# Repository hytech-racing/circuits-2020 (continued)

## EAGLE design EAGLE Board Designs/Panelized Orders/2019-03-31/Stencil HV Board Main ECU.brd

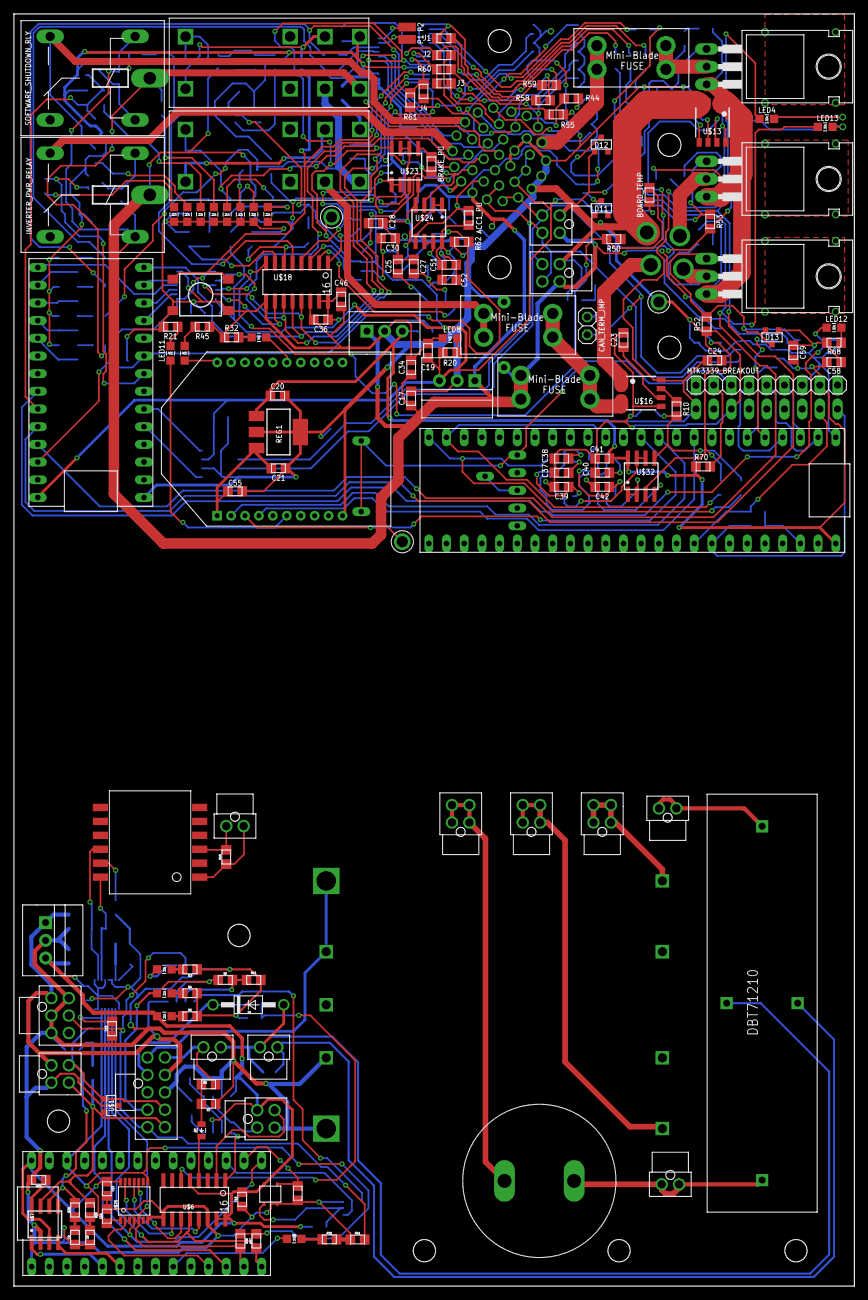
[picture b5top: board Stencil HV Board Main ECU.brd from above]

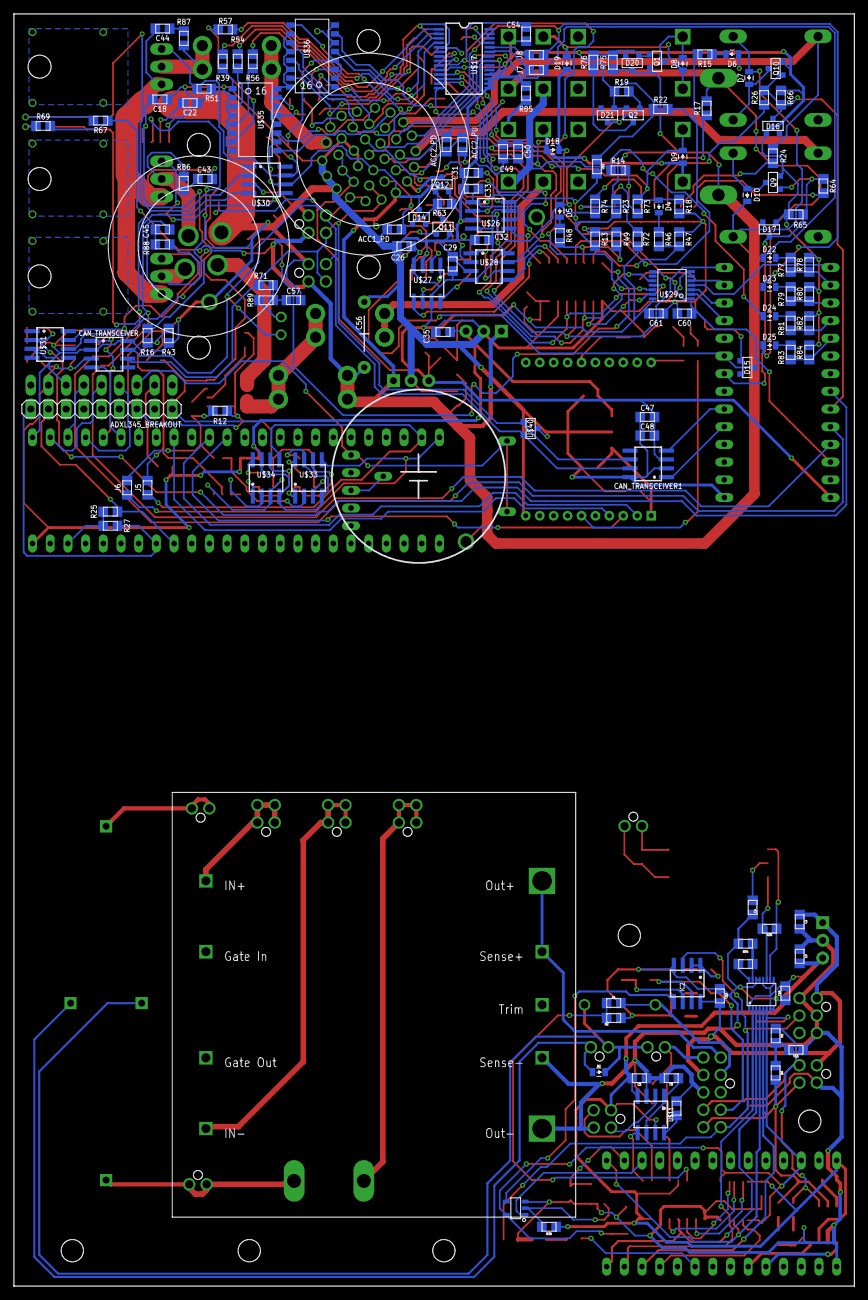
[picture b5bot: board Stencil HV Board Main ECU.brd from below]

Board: 2 copper layers, 120.7 x 182.6 mm, 291 parts (143 on the bottom side), 228 nets.

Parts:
5ABOARDFUSE, 5AFUSE, 5ASHUTDOWNFUSE: MINI-BLADE_FUSE_HOLDER
ACC1_PD, ACC1_PU, ACC2_PD, ACC2_PU: 10k; 0805
ADXL345_BREAKOUT: 1X09
BMS-OK: GREEN; LED-805
BMS_SHUTDOWN_RLY: RT424012; RELAY_DPDT
BOARD_TEMP: THERMISTOR_NCP210805; 0805
BRAKE_PU: 10k; 0805
C1: 180µF; LLS2V221MELZ
C2, C3, C17, C19, C34, C35: 10uF; 0805
C4: 27pF; 0805
C5, C6, C10, C12, C13, C14, C15, C16, C18, C24, C46, C54, C55: 0.1uF; 0805
C7: 530pF; 0805
C8, C9: 560pF; 0805
C11, C57: 4.7nF; 0805
C20, C21, C36, C47, C49, C51, C53, C58: 1uF; 0805
C22, C23, C25, C28, C31: 47nF; 0805
C26, C27, C29, C30, C32, C33, C38, C39, C41, C42, C48, C50, C52, C59, C60, C61: .1uF; 0805
C37, C40: 470pF; 0805
C43, C44, C45: 0805
C56: 470uF; CAP-PTH-LARGE
CAN_TERM_JMP: M02_SLIM; 1X02_SLIM
CAN_TRANSCEIVER, CAN_TRANSCEIVER1: MCP2551; SOIC-08
CURRENT: CURRENT; NANO-FIT_VERTICAL-4
D1: DIODE; DO-41
D2, D3, D4, D5, D6, D7, D8, D9, D10, D18, D19, D22, D23, D24, D25: TS4148 RYG; 0805_D
D11, D12, D13, D14, D15, D16, D17, D20, D21: MMBZ5246BLT1G; SOT23
DISCH+: DISCHARGE+; NANO-FIT_VERTICAL-2
HV+FUSED_1A-IMD+: HV+; NANO-FIT_VERTICAL-4
HV+UNFUSED: HV+UNFUSED; NANO-FIT_VERTICAL-2
HV-FUSED_1A-IMD-: HV-; NANO-FIT_VERTICAL-4
HV-UNFUSED_DISCHARGE-: HV-UNFUSED; NANO-FIT_VERTICAL-4
IC1: OKI-78SR-5; OKI-78SR
IC2: NE5532SOIC; SOIC-08
IMD: CONNECTOR-6NANO-FIT_VERTICAL-6; NANO-FIT_VERTICAL-6
IMD-OK: YELLOW; LED-805
IMD_SHUTDOWN_RLY: RT424009; RELAY_DPDT
INTERLOCK: INTERLOCK; NANO-FIT_VERTICAL-2
INVERTER_PWR_RELAY: G5LE; ZF112
ISO_SPI: ISO_SPI; NANO-FIT_VERTICAL-2
J1, J2, J3, J4, J5, J6, J7, J8: JUMPER; 0805
LED: BLUE; LED-805
LED1: White; LED-805
LED3, LED7, LED11: Green; LED-805
LED4, LED6, LED10, LED12, LED13, LED17, LED18: Red; LED-805
LED5, LED9: Yellow; LED-805
LED8: Purple; LED-805
LED14: Blue; LED-805
MAIN: MAIN; NANO-FIT_VERTICAL-10
MTK3339_BREAKOUT: 1X09
ON-LED: PURPLE; LED-805
P1, P2: SOLDER_PAD; SOLDER_PAD_XSMALL
POWER: POWER; NANO-FIT_VERTICAL-4
Q1, Q12: P-CHANNEL_MOSFET_DMP3099L-7; SOT23
Q2, Q9, Q10, Q11: SOT23
R1, R6, R15, R23, R46, R48, R77, R79, R81, R83: 43k; 0805
R2, R7, R13, R22, R47, R49, R78, R80, R82, R84: 12k; 0805
R3: 820; 0805
R4: 5k; 0805
R5, R20: 270; 0805
R8, R9, R71, R89: 60; 0805
R10, R16: 1K; 0805
R11, R30, R33, R34, R76: 1k; 0805
R12, R43: 2K; 0805
R14, R18, R36, R37, R41, R73: 2k; 0805
R17: 20k; 0805
R19, R42, R50, R51, R52, R53, R62, R63, R65, R66, R70, R75: 10k; 0805
R21, R74: 33; 0805
R24: 6.8k; 0805
R25, R27: 4.7k; 0805
R26: 1.2K; 0805
R28, R29, R40: 100; 0805
R31: 43; 0805
R32, R64, R67, R68, R69: 1.2k; 0805
R35: 120; 0805
R38: 430; 0805
R39, R54, R56, R57, R58, R59, R60, R61: 150; 0805
R44, R45, R55: 0; 0805
R72: 5.1k; 0805
R85: 20; 0805
R86, R87, R88: 0805
REG, REG3: 5V; OKI-78SR
REG1: LM3940; SOT223
RELAYS: RELAYS; NANO-FIT_VERTICAL-2
RF: 2k; 0805
S1: TACTILE_SWITCH_SMD_6.2MM_TALL
SOFTWARE_SHUTDOWN_RLY: G5LE; ZF112
U$1, U$40: CDSOT23-T24CAN-Q; SOT23
U$2: HM2102NLT
U$3: SN74LVC1G08; SOT-23-5
U$4: DBT71210
U$5: HV_DCDC_VI-J71-CZ
U$6, U$18: MCP3208SOIC; SOIC-16
U$7: MCP2551; SOIC-08
U$8: LTC6820; MSOP-16
U$9, U$12: TEENSY_3.2_SIMPLE
U$10: STWD100; SOT23-5
U$11: MAX7480; SOIC-08
U$13, U$16: ACS715_CURRENT_SENSOR; SOP8
U$14: TEENSY_3.5_EXT
U$15: XBEE
U$17: MCP23S17SSOP28; SSOP28
U$19, U$20, U$21: N-CHANNEL_MOSFET_IRF1324PBF; TO-220-H-HOLE
U$22: CR-2450/G1AN
U$23, U$24, U$32: MCP6002SOIC; SOIC-08
U$25, U$29: TXB0104TSSOP; TSSOP-14
U$26, U$27, U$28, U$33, U$34: SOIC-08
U$30, U$31: MC34152; SOIC-08
U$35, U$36: TLP291-4; 11-11F1
U$37, U$38, U$39: TEST_POINT
X1: CONNECTOR-37; AUTOSPORT_14-35
X2: CONNECTOR-4AUTOSPORT; AUTOSPORT_12-04
X3, X4: CONNECTOR-4NANO-FIT-VERTICAL-4; NANO-FIT_VERTICAL-4

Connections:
3.3V: R25.2, R27.2, U$14.3.3V
3.3V_MAIN_TEENSY: C60.1, U$12.3.3V, U$29.1, U$29.8
12VIN: U$16.1, U$16.2, X2.P$1
12VSUPPLY_DIV: C53.2, R13.1, R23.2, U$23.3
12VSUPPLY_READ: U$18.4, U$23.1, U$23.2
12VUNFUSED: 5ABOARDFUSE.L1, 5ABOARDFUSE.L2, 5ASHUTDOWNFUSE.L1, 5ASHUTDOWNFUSE.L2, U$16.3, U$16.4
+3V3: C14.1, C15.2, R36.1, R37.1, U$3.5, U$8.6, U$9.3.3V, U$25.1, U$25.8
+5V: C3.1, C5.1, C10.1, C13.1, C16.2, CURRENT.P$1, IC1.3, ON-LED.A, R38.1, U$6.5, U$6.15, U$6.16, U$7.3, U$8.1, U$8.7, U$8.8, U$8.9, U$8.12, U$9.VIN, U$10.VCC, U$11.4, U$11.7, U$25.14
+5V1: ACC1_PU.2, ACC2_PU.2, BOARD_TEMP.1, BRAKE_PU.2, C19.2, C26.1, C29.1, C32.1, C36.2, C46.2, C47.2, C48.2, C49.2, C50.2, C51.1, C52.1, C54.1, C61.1, CAN_TRANSCEIVER1.3, R20.1, R72.1, REG.3, U$12.VIN, U$17.9, U$17.18, U$18.15, U$18.16, U$23.8, U$24.8, U$26.4, U$26.7, U$27.4, U$27.7, U$28.4, U$28.7, U$29.14, U$38.P$1, X1.P$27, X1.P$28, X1.P$29
+12V: C2.1, C12.1, IC1.1, IC2.8, IMD.P$1, MAIN.P$7, POWER.P$1
+12V1: 5ABOARDFUSE.R1, 5ABOARDFUSE.R2, C17.2, C34.2, C56.1, D7.C, D10.C, D14.3, D20.3, INVERTER_PWR_RELAY.1, INVERTER_PWR_RELAY.P, Q1.2, Q12.2, R23.1, R63.1, R75.1, REG.1, REG3.1, SOFTWARE_SHUTDOWN_RLY.2, U$30.6, U$31.6, U$35.10, U$35.12, U$35.14, U$35.16, U$36.10, U$36.12, U$36.14, U$36.16, U$37.P$1, X1.P$10, X1.P$34, X3.P$1, X4.P$1
BMS_OK: D5.A, D21.3, Q2.1, R19.1, R74.1, X1.P$31
BMS_OK_3.3V: IC2.5, U$3.4
BMS_OK_10V: BMS-OK.A, IC2.7, MAIN.P$4, RF.2
BMS_OK_READ: R48.2, R49.1, U$18.6
BMS_OK_SW: BMS_SHUTDOWN_RLY.COIL+, D8.C, Q1.3
BMS_PWR_STEP: BMS_SHUTDOWN_RLY.3, BMS_SHUTDOWN_RLY.COIL-, D8.A, D19.A
BRAKE_LIGHT: Q12.3, X1.P$9
BRAKE_LIGHT_CTRL: D15.3, Q11.1, R62.2, U$12.D7(RX3)
CANH: MAIN.P$10, POWER.P$4, R8.2, R28.2, U$1.2, U$7.7
CANH1: CAN_TERM_JMP.1, CAN_TRANSCEIVER.7, CAN_TRANSCEIVER1.7, U$40.2, X1.P$12, X1.P$13, X3.P$4, X4.P$4
CANL: MAIN.P$9, POWER.P$3, R9.2, R29.2, U$1.1, U$7.6
CANL1: CAN_TRANSCEIVER.6, CAN_TRANSCEIVER1.6, R71.1, U$40.1, X1.P$11, X1.P$26, X3.P$3, X4.P$3
CHARGE_ENABLE: D1.C, MAIN.P$2, R1.1
COOLINGSENSE: J5.2, R16.2, R43.2, U$32.3
COOLINGSENSE_FILT: J5.1, U$14.A12, U$34.5
CS1_5V: U$18.10, U$29.13
CS1_TEENSY: U$12.D9(RX2), U$29.2
CS2_5V: U$17.11, U$29.12
CS2_TEENSY: U$12.D10(TX2), U$29.3
CS_LTC6820: U$8.5, U$9.D10(TX2)
CS_MCP3208_3.3V: U$9.D9(RX2), U$25.2
CURRENTSENSE2: C43.2, C44.2, C45.2, U$13.1, U$13.2, U$19.3, U$20.3, U$21.3
CUR_SENSE: CURRENT.P$2, U$11.2
DASH11_READ: R77.2, R78.1, U$12.A0
DASH12_READ: R79.2, R80.1, U$12.A1
DASH_1_EXTERN: R44.2, X1.P$1
DASH_1_INTER: R39.1, U$17.1
DASH_2_EXTERN: R55.2, X1.P$2
DASH_2_INTER: R54.1, U$17.2
DASH_3_EXTERN: U$35.11, X1.P$3
DASH_3_INTER: R56.1, U$17.3
DASH_4_EXTERN: U$35.9, X1.P$4
DASH_4_INTER: R57.1, U$17.4
DASH_5_EXTERN: J1.1, U$36.15, X1.P$18
DASH_5_INTER: J1.2, R58.1, U$17.5
DASH_6_EXTERN: J2.1, U$36.13, X1.P$19
DASH_6_INTER: J2.2, R59.1, U$17.6
DASH_7_EXTERN: J3.1, U$36.11, X1.P$20
DASH_7_INTER: J3.2, R60.1, U$17.7
DASH_8_EXTERN: J4.1, U$36.9, X1.P$21
DASH_8_INTER: J4.2, R61.1, U$17.8
DASH_9_EXTERN: U$17.21, X1.P$23
DASH_10_EXTERN: U$17.22, X1.P$32
DASH_11_EXTERN: D22.A, J7.1, X1.P$6
DASH_11_INTER: J7.2, U$17.23
DASH_12_EXTERN: D23.A, J8.1, X1.P$22
DASH_12_INTER: J8.2, U$17.24
DISCHARGE_RELAY_GND: D2.A, RELAYS.P$2, U$4.COIL-
ECUSENSE: J6.2, R10.2, R12.2, U$32.5
ECUSENSE_FILT: J6.1, U$14.A13, U$33.5
FAN1-: 5AFUSE.R1, 5AFUSE.R2, R87.1, U$20.2
FAN1CONTROL: LED4.A, U$12.A8, U$30.2
FAN1DRIVE: D12.3, R51.2, U$20.1, U$30.7
FAN2-: R86.1, U$19.2, X2.P$3
FAN2CONTROL: LED13.A, U$12.A9, U$30.4
FAN2DRIVE: D11.3, R53.2, U$19.1, U$30.5
GND: C2.2, C3.2, C4.2, C5.2, C6.2, C7.2, C8.1, C9.1, C10.2, C11.1, C12.2, C13.2, C14.2, C15.1, C16.1, CURRENT.P$4, IC1.2, IC2.4, IMD.P$2, IMD.P$3, IMD.P$4, MAIN.P$8, POWER.P$2, R2.1, R3.1, R4.2, R5.2, R7.1, R11.1, R30.1, R31.2, R34.2, R41.2, R42.2, U$1.3, U$3.3, U$5.8SENSE-, U$5.9VOUT-, U$6.9, U$6.14, U$7.2, U$8.13, U$8.14, U$9.GND, U$10.EN, U$10.GND, U$11.3, U$25.7
GND1: ACC1_PD.2, ACC2_PD.2, ADXL345_BREAKOUT.3, BMS_SHUTDOWN_RLY.4, C17.1, C18.2, C19.1, C20.2, C21.1, C22.2, C23.2, C24.2, C25.2, C26.2, C27.1, C28.2, C29.2, C30.1, C31.2, C32.2, C33.1, C34.1, C35.1, C36.1, C37.2, C38.2, C39.1, C40.2, C41.2, C42.1, C46.1, C47.1, C48.1, C49.1, C50.1, C51.2, C52.2, C53.1, C54.2, C55.2, C56.2, C57.2, C58.1, C59.1, C60.2, C61.2, CAN_TRANSCEIVER.2, CAN_TRANSCEIVER.8, CAN_TRANSCEIVER1.2, CAN_TRANSCEIVER1.8, D11.1, D12.1, D13.1, D15.1, D16.1, D17.1, D21.1, LED3.C, LED5.C, LED6.C, LED7.C, LED8.C, LED9.C, LED17.C, LED18.C, MTK3339_BREAKOUT.7, Q2.2, Q9.2, Q10.2, Q11.2, R12.1, R13.2, R18.2, R19.2, R21.1, R22.2, R32.1, R43.1, R45.1, R47.2, R49.2, R50.1, R51.1, R52.1, R53.1, R62.1, R65.2, R66.2, R67.2, R68.2, R69.2, R78.2, R80.2, R82.2, R84.2, R85.2, REG.2, REG1.2, REG1.4, REG3.2, S1.B1, S1.B2, U$12.GND, U$13.3, U$13.4, U$13.5, U$14.GND, U$15.10, U$16.5, U$17.10, U$17.15, U$17.16, U$17.17, U$18.9, U$18.14, U$23.4, U$24.4, U$26.3, U$27.3, U$28.3, U$29.7, U$30.3, U$31.3, U$32.4, U$33.3, U$34.3, U$35.2, U$35.4, U$35.6, U$35.8, U$36.2, U$36.4, U$36.6, U$36.8, U$39.P$1, U$40.3, X1.P$14, X1.P$15, X1.P$16, X1.P$30, X1.P$35, X1.P$36, X2.P$4, X3.P$2, X4.P$2
HV+FUSED_1A: HV+FUSED_1A-IMD+.P$1, HV+FUSED_1A-IMD+.P$2, HV+FUSED_1A-IMD+.P$3, HV+FUSED_1A-IMD+.P$4, U$5.1VIN+
HV+UNFUSED: C1.P$1, HV+UNFUSED.P$1, HV+UNFUSED.P$2, U$4.CONTACT1
HV+UNFUSED_FSAE_DISCHARGE: DISCH+.P$1, DISCH+.P$2, U$4.CONTACT2
HV-FUSED_1A: HV-FUSED_1A-IMD-.P$1, HV-FUSED_1A-IMD-.P$2, HV-FUSED_1A-IMD-.P$3, HV-FUSED_1A-IMD-.P$4, U$5.4VIN-
HV-UNFUSED: C1.P$2, HV-UNFUSED_DISCHARGE-.P$1, HV-UNFUSED_DISCHARGE-.P$2, HV-UNFUSED_DISCHARGE-.P$3, HV-UNFUSED_DISCHARGE-.P$4
IM: R35.1, U$2.P$10, U$8.10
IMD_PWR_STEP: D9.A, D18.A, IMD_SHUTDOWN_RLY.3, IMD_SHUTDOWN_RLY.COIL-
INVERTER_CTRL: D17.3, Q9.1, R64.1, R65.1, U$12.D6
INVERTER_SUPPLY: INVERTER_PWR_RELAY.S, X1.P$7
IP: R35.2, U$2.P$12, U$8.11
ISOSPI-M: ISO_SPI.P$2, R40.2, U$2.P$3
ISOSPI-P: ISO_SPI.P$1, R40.1, U$2.P$1
LATCH_EXT_BUTTON: D18.C, D19.C, LED1.C, S1.A1, S1.A2, X1.P$37
MISO: R37.2, U$6.12, U$8.3, U$9.D12
MISO_TEENSY: U$12.D12, U$17.14, U$18.12
MOSI_5V: U$6.11, U$25.10
MOSI_5V1: U$17.13, U$18.11, U$29.10
MOSI_TEENSY: R36.2, U$8.2, U$9.D11, U$25.5
MOSI_TEENSY1: U$12.D11, U$29.5
MTK3339_DIN: MTK3339_BREAKOUT.6, U$14.D1(TX1)
MTK3339_DOUT: MTK3339_BREAKOUT.5, U$14.D0(RX1)
MTK3339_FIX: MTK3339_BREAKOUT.4, U$14.D2
unnamed: U$6.1, U$11.5
unnamed: C6.1, U$11.1, U$11.6
unnamed: ON-LED.C, R5.1
unnamed: C7.1, U$11.8
unnamed: LED7.A, R17.2
unnamed: LED18.A, R24.2
unnamed: U$6.10, U$25.13
unnamed: LED8.A, R20.2
unnamed: D3.A, R6.2, R7.2
unnamed: D3.C, U$6.4
unnamed: C11.2, R8.1, R9.1
unnamed: IC2.6, R11.2, RF.1
unnamed: R10.1, U$16.7
unnamed: R16.1, U$13.7
unnamed: C23.1, U$16.6
unnamed: CAN_TRANSCEIVER.4, U$14.D4(CANRX)
unnamed: CAN_TRANSCEIVER.1, U$14.D3(CANTX)
unnamed: CAN_TRANSCEIVER1.4, U$12.D4(CANRX)
unnamed: LED5.A, R14.2
unnamed: U$24.6, U$24.7, U$27.2
unnamed: U$23.6, U$23.7, U$26.2
unnamed: CAN_TRANSCEIVER1.1, U$12.D3(CANTX)
unnamed: U$24.1, U$24.2, U$28.2
unnamed: R1.2, R2.2, U$6.6
unnamed: U$7.1, U$9.D3(CANTX)
unnamed: R30.2, U$7.8
unnamed: C8.2, R28.1
unnamed: C9.2, R29.1
unnamed: LED.C, R31.1
unnamed: D4.C, R46.1
unnamed: R33.1, U$8.16
unnamed: R33.2, R34.1, U$8.15
unnamed: D5.C, R48.1
unnamed: D6.C, R15.1
unnamed: C4.1, U$2.P$11
unnamed: U$7.4, U$9.D4(CANRX)
unnamed: LED.A, U$9.D7(RX3)
unnamed: R38.2, U$3.2, U$10.WDO
unnamed: LED11.C, R21.2
unnamed: U$3.1, U$9.A1
unnamed: LED10.C, R32.2
unnamed: IC2.1, IC2.2, IMD-OK.A
unnamed: LED14.C, R45.2
unnamed: BMS-OK.C, R4.1
unnamed: IMD-OK.C, R3.2
unnamed: LED17.A, R26.2
unnamed: LED11.A, U$15.6
unnamed: C22.1, U$13.6
unnamed: LED10.A, U$15.15
unnamed: R42.1, U$9.A0, U$10.WDI
unnamed: R39.2, U$35.1
unnamed: 5AFUSE.L1, 5AFUSE.L2, X1.P$17
unnamed: C27.2, U$27.1, U$27.6
unnamed: C25.1, U$27.8
unnamed: C30.2, U$28.1, U$28.6
unnamed: C28.1, U$28.8
unnamed: C33.2, U$26.1, U$26.6
unnamed: C31.1, U$26.8
unnamed: R44.1, U$35.15
unnamed: R54.2, U$35.3
unnamed: R55.1, U$35.13
unnamed: R56.2, U$35.5
unnamed: LED14.A, U$15.20
unnamed: R57.2, U$35.7
unnamed: R58.2, U$36.1
unnamed: R59.2, U$36.3
unnamed: R60.2, U$36.5
unnamed: R61.2, U$36.7
unnamed: D14.1, Q11.3, Q12.1, R63.2
unnamed: LED6.A, R64.2
unnamed: U$14.GND_2, U$22.-
unnamed: D10.A, INVERTER_PWR_RELAY.2, Q9.3
unnamed: D7.A, Q10.3, SOFTWARE_SHUTDOWN_RLY.1
unnamed: U$32.1, U$32.2, U$34.2
unnamed: U$32.6, U$32.7, U$33.2
unnamed: C39.2, U$33.1, U$33.6
unnamed: C37.1, U$33.8
unnamed: C42.2, U$34.1, U$34.6
unnamed: C40.1, U$34.8
unnamed: LED4.C, R67.1
unnamed: LED12.C, R68.1
unnamed: LED13.C, R69.1
unnamed: MTK3339_BREAKOUT.2, R70.2
unnamed: LED1.A, R72.2
unnamed: LED9.A, R73.2
unnamed: LED3.A, R74.2
unnamed: D20.1, Q1.1, R75.2, R76.2
unnamed: Q2.3, R76.1
unnamed: D22.C, R77.1
unnamed: D23.C, R79.1
unnamed: D24.C, R81.1
unnamed: D25.C, R83.1
unnamed: IMD_SHUTDOWN_RLY.4, R85.1
unnamed: P1.P$1, U$17.25
unnamed: P2.P$1, U$17.26
unnamed: C44.1, R87.2
unnamed: C43.1, R86.2
unnamed: C45.1, R88.2
unnamed: CAN_TERM_JMP.2, R89.2
unnamed: C57.1, R71.2, R89.1
OKHS: IC2.3, IMD.P$5, MAIN.P$5, R41.1
OKHS1: D4.A, D9.C, IMD_SHUTDOWN_RLY.COIL+, R18.1, R73.1, X1.P$33
OKHS_READ: R46.2, R47.1, U$18.7
PUMP1-: R88.1, U$21.2, X2.P$2
PUMPCONTROL: LED12.A, U$12.A6, U$31.2
PUMPDRIVE: D13.3, R52.2, U$21.1, U$31.7
READ_ACCEL1: U$18.2, U$27.5
READ_ACCEL2: U$18.3, U$28.5
READ_BRAKE: U$18.1, U$26.5
SCK_5V: U$6.13, U$25.11
SCK_5V1: U$17.12, U$18.13, U$29.11
SCK_TEENSY: U$8.4, U$9.D13, U$25.4
SCK_TEENSY1: U$12.D13, U$29.4
SCL: ADXL345_BREAKOUT.9, R27.1, U$14.A5
SDA: ADXL345_BREAKOUT.8, R25.1, U$14.A4
SHUTDOWN_A: 5ASHUTDOWNFUSE.R1, 5ASHUTDOWNFUSE.R2, IMD_SHUTDOWN_RLY.6
SHUTDOWN_B: BMS_SHUTDOWN_RLY.6, D24.A, IMD_SHUTDOWN_RLY.5, R14.1
SHUTDOWN_B_READ: R81.2, R82.1, U$12.A2
SHUTDOWN_C: BMS_SHUTDOWN_RLY.5, D25.A, R17.1, SOFTWARE_SHUTDOWN_RLY.P
SHUTDOWN_C_READ: R83.2, R84.1, U$12.A3
SHUTDOWN_D: D6.A, R24.1, SOFTWARE_SHUTDOWN_RLY.S, X1.P$5
SHUTDOWN_G: INTERLOCK.P$1, MAIN.P$6, R6.1
SHUTDOWN_H: D1.A, D2.C, INTERLOCK.P$2, RELAYS.P$1, U$4.COIL+
SHUTDOWN_OUT_READ: R15.2, R22.1, U$18.5
SIGNAL_ACCEL1: ACC1_PD.1, ACC1_PU.1, U$24.5, X1.P$25
SIGNAL_ACCEL2: ACC2_PD.1, ACC2_PU.1, U$24.3, X1.P$24
SIGNAL_BRAKE: BRAKE_PU.1, U$23.5, X1.P$8
SOFTWARE_SHUTDOWN: D16.3, Q10.1, R26.1, R66.1, U$12.A7
TELEMETRY5V: ADXL345_BREAKOUT.1, C18.1, C20.1, C24.1, C35.2, C38.1, C41.1, C58.2, C59.2, CAN_TRANSCEIVER.3, MTK3339_BREAKOUT.8, R70.1, REG1.1, REG3.3, U$13.8, U$14.VIN, U$16.8, U$32.8, U$33.4, U$33.7, U$34.4, U$34.7
TEMPSENSE: BOARD_TEMP.2, R50.2, U$18.8
TEMP_SENSE: CURRENT.P$3, U$6.2
TSAL+: MAIN.P$1, U$5.5VOUT+, U$5.6SENSE+
VBAT_RTC: MTK3339_BREAKOUT.3, U$14.VBAT, U$22.+_0, U$22.+_1
VCC: C21.2, C55.1, REG1.3, U$15.1
XB8: U$14.D7(RX3), U$15.4
XBDI: U$14.D10(TX2), U$15.3
XBDO: U$14.D9(RX2), U$15.2

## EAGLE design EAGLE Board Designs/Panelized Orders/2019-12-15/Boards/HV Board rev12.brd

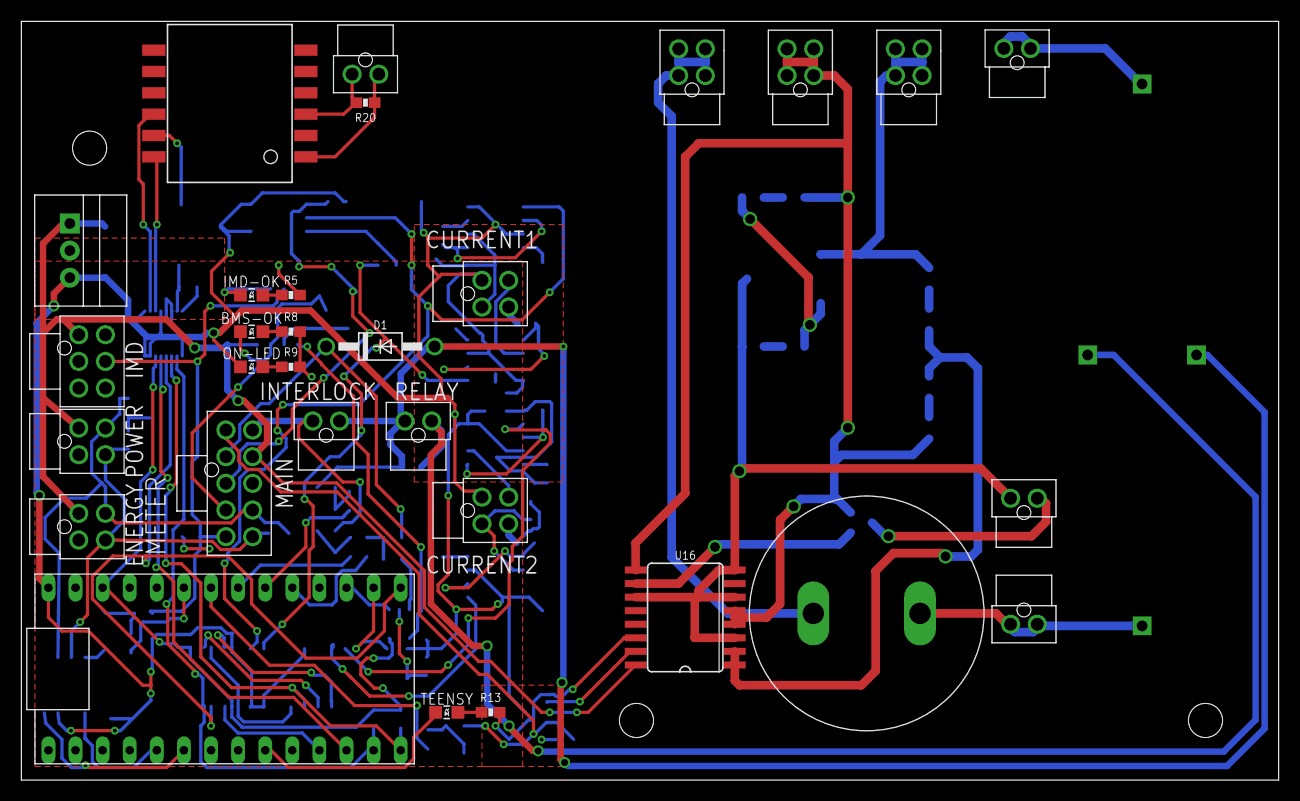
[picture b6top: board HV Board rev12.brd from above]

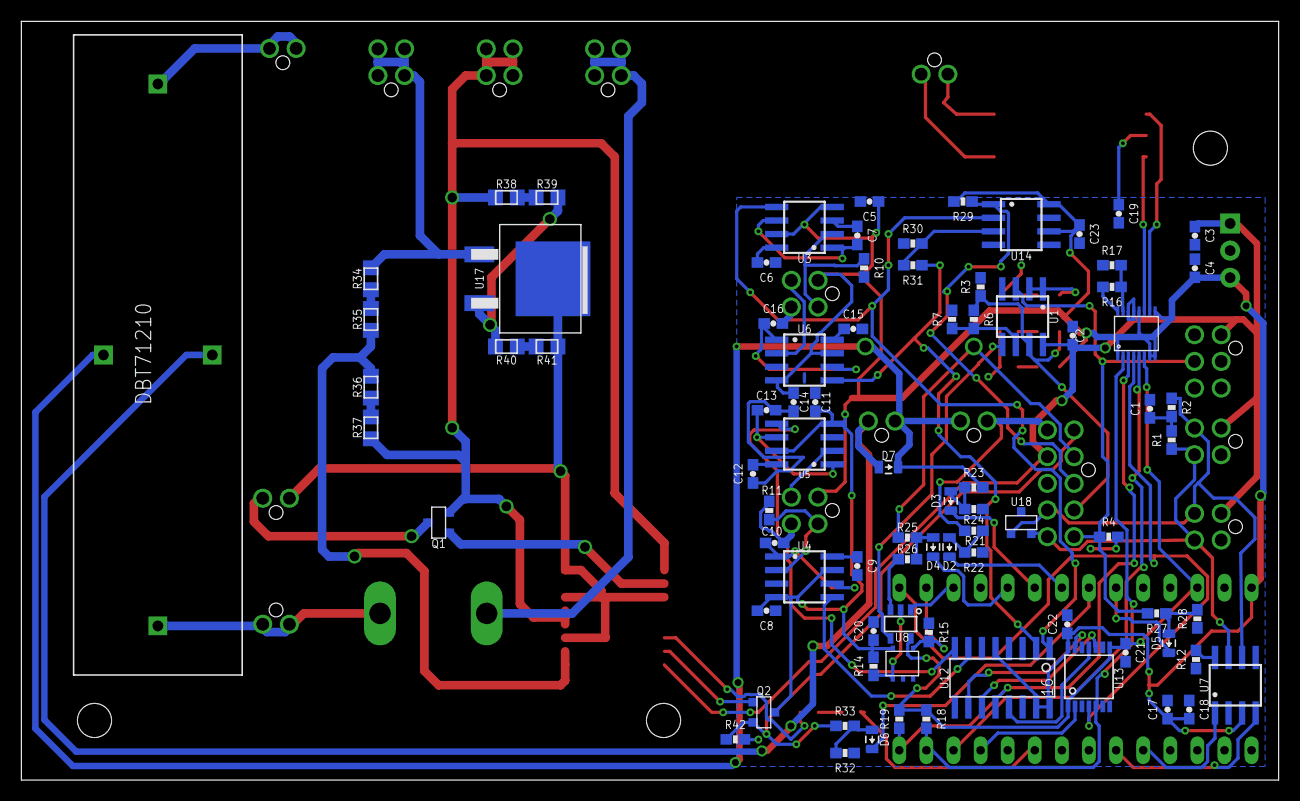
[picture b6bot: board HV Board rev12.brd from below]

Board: 2 copper layers, 117.9 x 71.1 mm, 113 parts (83 on the bottom side), 86 nets.

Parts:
BMS-OK: GREEN; LED-805
C1: 4.7nF; 0603-CAP
C2, C5, C7, C8, C10, C11, C13, C14, C16, C17, C18, C20, C21, C22, C23: 0.1uF; 0603-CAP
C3, C4: 10uF; 0603-CAP
C6, C9, C12, C15: 530pF; 0603-CAP
C19: 27pF; 0603-CAP
C24: 180µF; LLS2V221MELZ
CURRENT1, CURRENT2: CURRENT; NANO-FIT_VERTICAL-4
D1: DIODE; DO-41
D2, D3, D4, D5, D6, D7: TS4148 RYG; 0805_D
DISCH+: DISCHARGE+; NANO-FIT_VERTICAL-2
ENERGYMETER: ENERGY METER; NANO-FIT_VERTICAL-4
HV+FUSED_1A-IMD+: HV+; NANO-FIT_VERTICAL-4
HV+UNFUSED: HV+UNFUSED; NANO-FIT_VERTICAL-2
HV-FUSED_1A-IMD-: HV-; NANO-FIT_VERTICAL-4
HV-UNFUSED_DISCHARGE-: HV-UNFUSED; NANO-FIT_VERTICAL-4
IMD: IMD; NANO-FIT_VERTICAL-6
IMD-OK: YELLOW; LED-805
INDICATOR: INDICATOR; NANO-FIT_VERTICAL-2
INTERLOCK: INTERLOCK; NANO-FIT_VERTICAL-2
ISO_SPI: ISO_SPI; NANO-FIT_VERTICAL-2
MAIN: MAIN; NANO-FIT_VERTICAL-10
ON-LED: PURPLE; LED-805
POWER: POWER; NANO-FIT_VERTICAL-4
Q1, Q2: DMG3406L; SOT23
R1, R2: 60; 0603-RES
R3, R4, R7, R8, R18, R19, R29, R42: 2k; 0603-RES
R5: 820; 0603-RES
R6: 4k; 0603-RES
R9: 270; 0603-RES
R10, R11, R15: 10K; 0603-RES
R12, R16, R17: 1k; 0603-RES
R13: 43; 0603-RES
R14: 430; 0603-RES
R20: 100; 0603-RES
R21, R23, R25, R27: 43k; 0603-RES
R22, R24, R26, R28: 12k; 0603-RES
R30, R32, R33: 5K; 0603-RES
R31: 261; 0603-RES
R34, R35: 510k; 0805
R36: 14k; 0805
R37: 1.4k; 0805
R38, R39: 20k; 0805
R40, R41: 2k; 0805
RELAY: RELAY; NANO-FIT_VERTICAL-2
TEENSY: BLUE; LED-805
TEENSY3.2: TEENSY_3.2_SIMPLE
U1: OPA2172; SOIC-08
U2: OKI-78SR-5; OKI-78SR
U3, U4, U5, U6: MAX7480; SOIC-08
U7: MCP2551; SOIC-08
U8: SN74LVC1G08; SOT-23-5
U9: LTC6820; MSOP-16
U10: STWD100; SOT23-5
U11: HM2102NLT
U12: MCP3208SOIC; SOIC-16
U13: TXB0104TSSOP; TSSOP-14
U14: MCP6542SOIC; SOIC-08
U15: DBT71210
U16: UCC21520A; SO16-DW
U17: LR8; TO-252
U18: CDSOT23-T24CAN-Q; SOT23

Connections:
60V_THRESHOLD_SIGNAL: MAIN.P$1, Q2.2, R33.1, R42.1
60V_THRESHOLD_TEENSY: D6.C, TEENSY3.2.A6
+3V3: C21.1, R18.1, R19.1, TEENSY3.2.3.3V, U8.5, U9.6, U13.1, U13.8
+5V: C4.1, C5.1, C8.1, C11.1, C14.1, C17.1, C18.1, C20.1, C22.1, C23.1, CURRENT1.P$1, CURRENT2.P$1, ON-LED.A, Q2.3, R14.1, R29.2, TEENSY3.2.VIN, U2.3, U3.4, U3.7, U4.4, U4.7, U5.4, U5.7, U6.4, U6.7, U7.3, U9.1, U9.7, U9.8, U9.9, U9.12, U10.VCC, U12.5, U12.15, U12.16, U13.14, U14.6, U14.8
+12V: C2.1, C3.1, ENERGYMETER.P$1, IMD.P$1, MAIN.P$7, POWER.P$1, U1.8, U2.1, U16.16
BMS_OK_3.3V: U1.5, U8.4
BMS_OK_10V: BMS-OK.A, MAIN.P$4, R3.1, R6.2, U1.7
BSPD_CURR_REFERENCE: R30.2, R31.1, U14.3
BSPD_CURR_SIGNAL: MAIN.P$3, R29.1, U14.1
CANH: ENERGYMETER.P$4, MAIN.P$10, POWER.P$4, R1.2, U7.7, U18.2
CANL: ENERGYMETER.P$3, MAIN.P$9, POWER.P$3, R2.2, U7.6, U18.1
CHARGE_ENABLE: D1.C, MAIN.P$2, R25.1
CHARGE_ENABLE_TEENSY: D4.C, TEENSY3.2.A3
CS_LTC6820: TEENSY3.2.D10(TX2), U9.5
CS_MCP3208_3.3V: TEENSY3.2.D9(RX2), U13.2
CURR1_SENSE: CURRENT1.P$2, R10.1, U3.2
CURR1_SENSE_FILTERED: U3.5, U12.1, U14.2
CURR2_SENSE: CURRENT2.P$2, R11.1, U4.2
CURR2_SENSE_FILTERED: U4.5, U12.7
DISCHARGE_RELAY_GND: D7.A, RELAY.P$2, U15.COIL-
GND: C1.1, C2.2, C3.2, C4.2, C5.2, C6.2, C7.2, C8.2, C9.2, C10.2, C11.2, C12.2, C13.2, C14.2, C15.2, C16.2, C17.2, C18.2, C19.2, C20.2, C21.2, C22.2, C23.2, CURRENT1.P$4, CURRENT2.P$4, ENERGYMETER.P$2, IMD.P$2, IMD.P$3, IMD.P$4, MAIN.P$8, POWER.P$2, R3.2, R4.2, R5.1, R7.1, R8.2, R9.2, R10.2, R11.2, R12.1, R13.2, R15.2, R17.2, R22.1, R24.1, R26.1, R28.1, R30.1, R32.1, R42.2, TEENSY3.2.AGND, TEENSY3.2.GND, U1.4, U2.2, U3.3, U4.3, U5.3, U6.3, U7.2, U8.3, U9.13, U9.14, U10.EN, U10.GND, U12.4, U12.9, U12.14, U13.7, U14.4, U14.5, U16.14, U18.3
HV+FUSED_1A: HV+FUSED_1A-IMD+.P$1, HV+FUSED_1A-IMD+.P$2, HV+FUSED_1A-IMD+.P$3, HV+FUSED_1A-IMD+.P$4, R34.2, U17.1
HV+UNFUSED: C24.P$1, HV+UNFUSED.P$1, HV+UNFUSED.P$2, U15.CONTACT1
HV+UNFUSED_FSAE_DISCHARGE: DISCH+.P$1, DISCH+.P$2, U15.CONTACT2
HV-FUSED_1A: HV-FUSED_1A-IMD-.P$1, HV-FUSED_1A-IMD-.P$2, HV-FUSED_1A-IMD-.P$3, HV-FUSED_1A-IMD-.P$4, Q1.2, R37.1, R38.2, U16.4, U16.5, U16.9
HV-UNFUSED: C24.P$2, HV-UNFUSED_DISCHARGE-.P$1, HV-UNFUSED_DISCHARGE-.P$2, HV-UNFUSED_DISCHARGE-.P$3, HV-UNFUSED_DISCHARGE-.P$4
IM: U9.10, U11.P$10
IP: U9.11, U11.P$12
ISOSPI-M: ISO_SPI.P$2, R20.2, U11.P$3
ISOSPI-P: ISO_SPI.P$1, R20.1, U11.P$1
MISO: R19.2, TEENSY3.2.D12, U9.3, U12.12
MOSI_5V: U12.11, U13.10
MOSI_TEENSY: R18.2, TEENSY3.2.D11, U9.2, U13.5
unnamed: INDICATOR.P$2, Q1.3
unnamed: C7.1, U3.1, U3.6
unnamed: ON-LED.C, R9.1
unnamed: C6.1, U3.8
unnamed: U12.10, U13.13
unnamed: D2.A, R21.2, R22.2
unnamed: D4.A, R25.2, R26.2
unnamed: D6.A, R32.2, R33.2
unnamed: C1.2, R1.1, R2.1
unnamed: R6.1, R7.2, U1.6
unnamed: D3.A, R23.2, R24.2
unnamed: R34.1, R35.1
unnamed: R39.1, R40.1, U17.3
unnamed: R35.2, R36.2, U16.1, U16.2
unnamed: R36.1, R37.2
unnamed: Q2.1, U16.15
unnamed: D5.A, R27.2, R28.2
unnamed: Q1.1, U16.10
unnamed: INDICATOR.P$1, R41.2, U16.3, U16.6, U16.8, U16.11, U17.2(TAB)
unnamed: TEENSY3.2.D3(CANTX), U7.1
unnamed: R12.2, U7.8
unnamed: R13.1, TEENSY.C
unnamed: R16.1, U9.16
unnamed: R16.2, R17.1, U9.15
unnamed: C19.1, U11.P$11
unnamed: TEENSY3.2.D4(CANRX), U7.4
unnamed: TEENSY.A, TEENSY3.2.D7(RX3)
unnamed: R14.2, U8.2, U10.WDO
unnamed: TEENSY3.2.A1, U8.1
unnamed: IMD-OK.A, U1.1, U1.2
unnamed: R40.2, R41.1
unnamed: BMS-OK.C, R8.1
unnamed: IMD-OK.C, R5.2
unnamed: R38.1, R39.2
unnamed: C16.1, U6.1, U6.6
unnamed: C15.1, U6.8
unnamed: R15.1, TEENSY3.2.A0, U10.WDI
unnamed: C10.1, U4.1, U4.6
unnamed: C9.1, U4.8
unnamed: C13.1, U5.1, U5.6
unnamed: C12.1, U5.8
OKHS: IMD.P$5, MAIN.P$5, R4.1, R27.1, U1.3
OKHS_TEENSY: D5.C, TEENSY3.2.A7
REF1_SENSE: CURRENT1.P$3, U6.2
REF1_SENSE_FILTERED: R31.2, U6.5, U12.2
REF2_SENSE: CURRENT2.P$3, U5.2
REF2_SENSE_FILTERED: U5.5, U12.8
SCK_5V: U12.13, U13.11
SCK_TEENSY: TEENSY3.2.D13, U9.4, U13.4
SHUTDOWN_G: INTERLOCK.P$1, MAIN.P$6, R21.1
SHUTDOWN_G_TEENSY: D2.C, TEENSY3.2.A5
SHUTDOWN_H: D1.A, D7.C, INTERLOCK.P$2, R23.1, RELAY.P$1, U15.COIL+
SHUTDOWN_H_TEENSY: D3.C, TEENSY3.2.A4
